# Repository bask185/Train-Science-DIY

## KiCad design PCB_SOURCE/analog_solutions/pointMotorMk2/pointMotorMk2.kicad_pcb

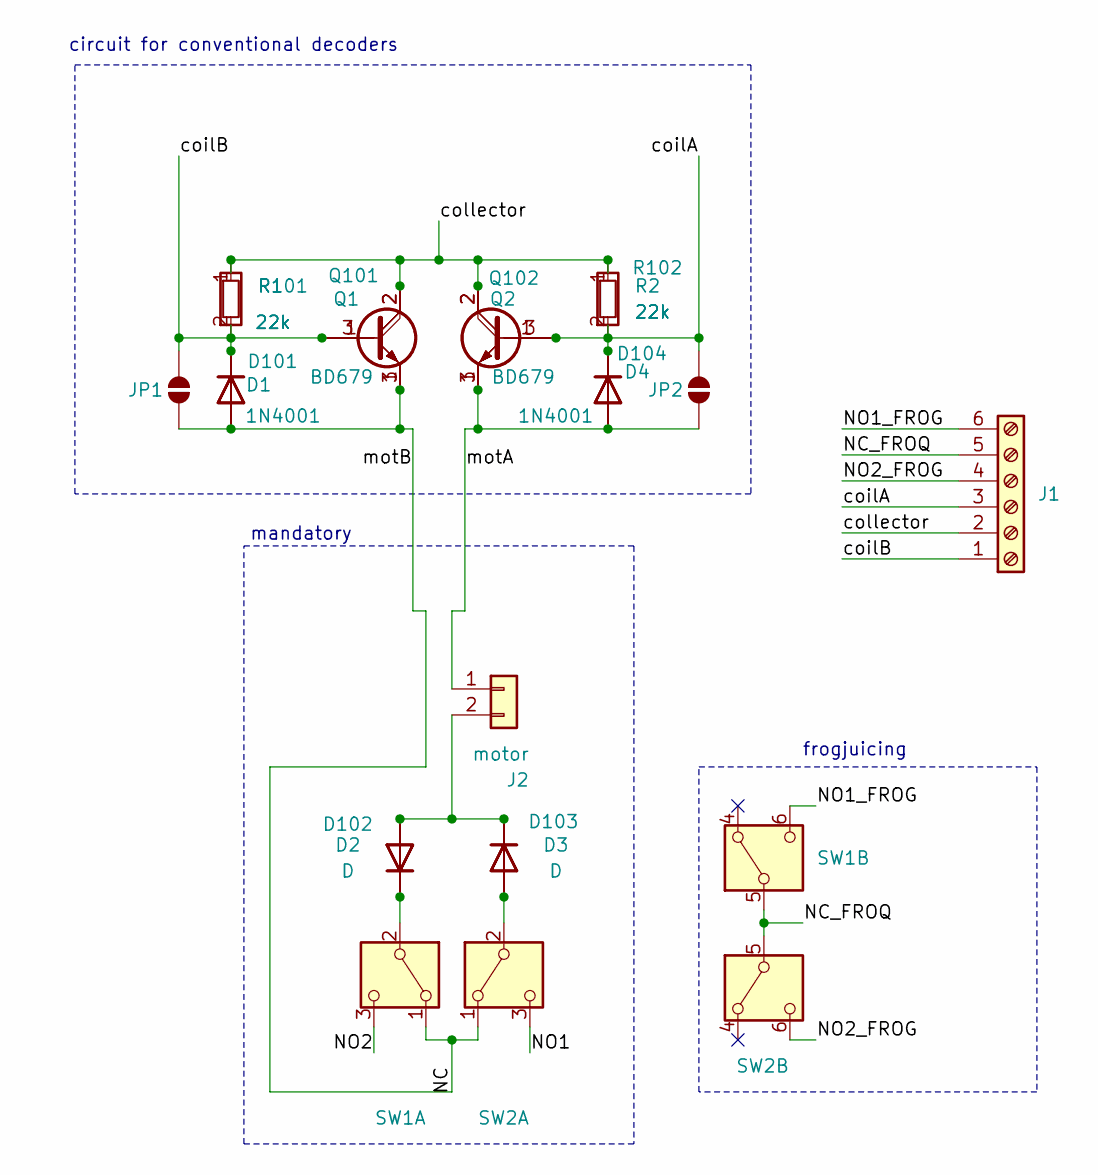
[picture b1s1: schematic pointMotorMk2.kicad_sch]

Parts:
D1, D4: 1N4001; D_DO-34_SOD68_P7.62mm_Horizontal
D2, D3: D; D_DO-34_SOD68_P7.62mm_Horizontal
D101, D102, D103, D104: SS26F; D_SMA; JLCPCB Part# C2758577
J1: Screw_Terminal_01x06; PhoenixContact_MCV_1,5_6-G-3.5_1x06_P3.50mm_Vertical
J2: motor; N20_motor_Mk2
JP1, JP2: SolderJumper_2_Open; SolderJumper-2_P1.3mm_Open_RoundedPad1.0x1.5mm
Q1, Q2: BD679; TO-126-3_Vertical
Q101, Q102: 4A_DARLINGTON; SOT-89-3; JLCPCB Part# C155228
R1, R2: 22k; R_Axial_DIN0204_L3.6mm_D1.6mm_P7.62mm_Horizontal
R101, R102: 22k; R_0805_handsolder-smalltext; JLCPCB Part# C17560
SW1, SW2: SW_DPDT_x2; DPDT_LIMIT_SWITCH

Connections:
/NC: D1.2 (A), D101.2 (A), JP1.1 (A), Q1.1 (E), Q101.3 (E), SW1.1 (A), SW2.1 (A)
/NC_FROQ: J1.5, SW1.5 (B), SW2.5 (B)
/NO1: SW2.3 (C)
/NO1_FROG: J1.6, SW1.6 (C)
/NO2: SW1.3 (C)
/NO2_FROG: J1.4, SW2.6 (C)
/coilA: D4.1 (K), D104.1 (K), J1.3, JP2.2 (B), Q2.3 (B), Q102.1 (B), R2.2, R102.2
/coilB: D1.1 (K), D101.1 (K), J1.1, JP1.2 (B), Q1.3 (B), Q101.1 (B), R1.2, R101.2
/collector: J1.2, Q1.2 (C), Q2.2 (C), Q101.2 (C), Q102.2 (C), R1.1, R2.1, R101.1, R102.1
/motA: D4.2 (A), D104.2 (A), J2.1, JP2.1 (A), Q2.1 (E), Q102.3 (E)
unnamed: D2.2 (A), D3.1 (K), D102.2 (A), D103.1 (K), J2.2
unnamed: D2.1 (K), D102.1 (K), SW1.2 (B)
unnamed: D3.2 (A), D103.2 (A), SW2.2 (B)

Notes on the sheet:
frogjuicing
mandatory
circuit for conventional decoders

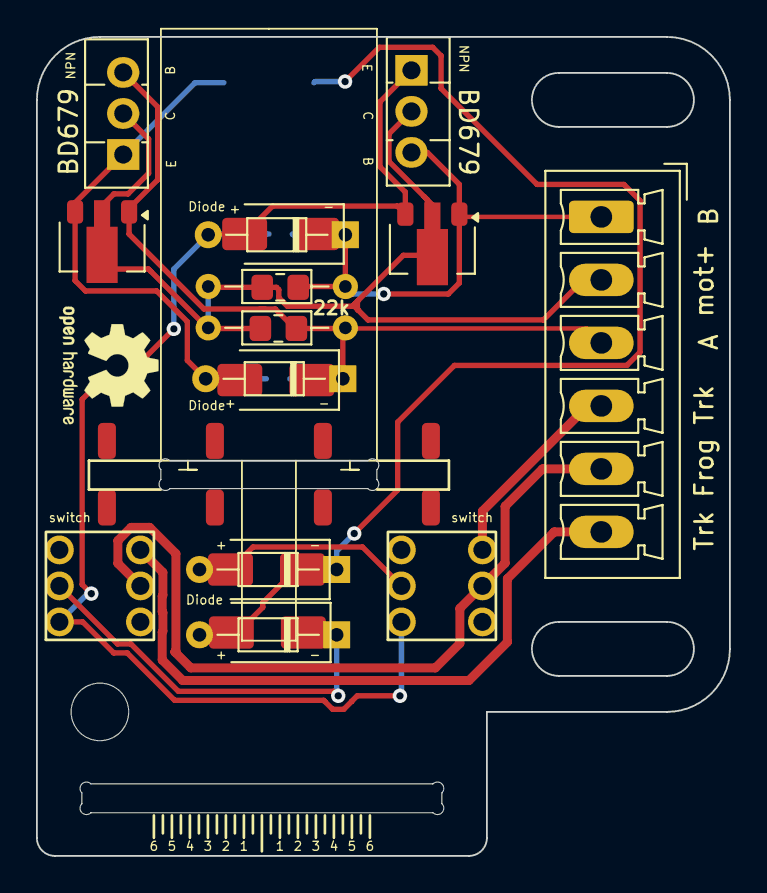
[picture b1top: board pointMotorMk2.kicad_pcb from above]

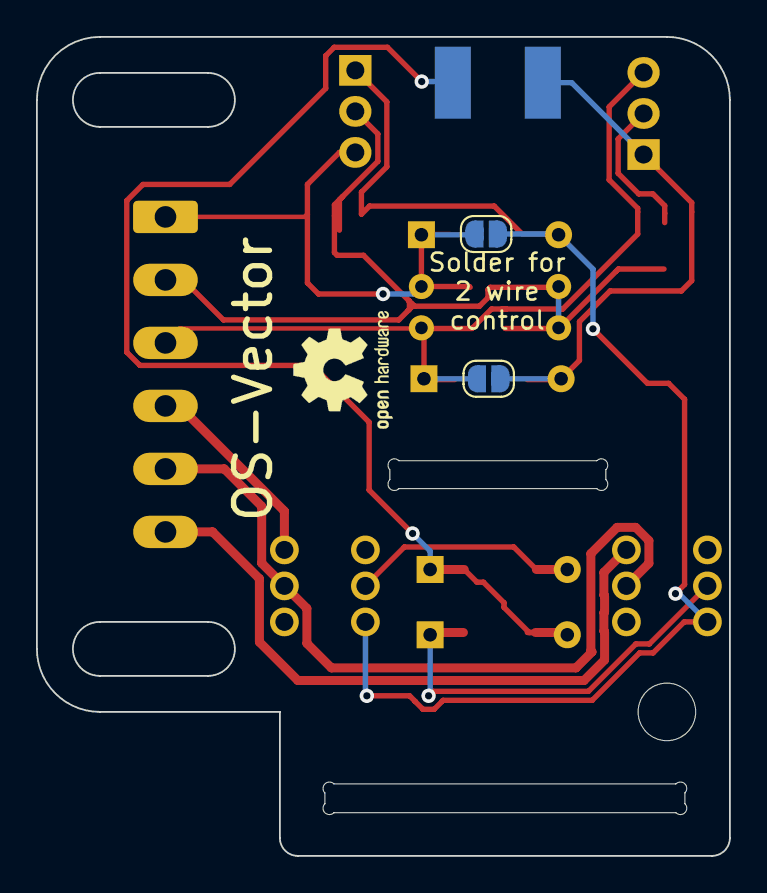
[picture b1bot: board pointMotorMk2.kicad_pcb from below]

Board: 2 copper layers, 38.5 x 45.5 mm, 23 parts (2 on the bottom side), 11 nets.

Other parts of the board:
**: slideGuide

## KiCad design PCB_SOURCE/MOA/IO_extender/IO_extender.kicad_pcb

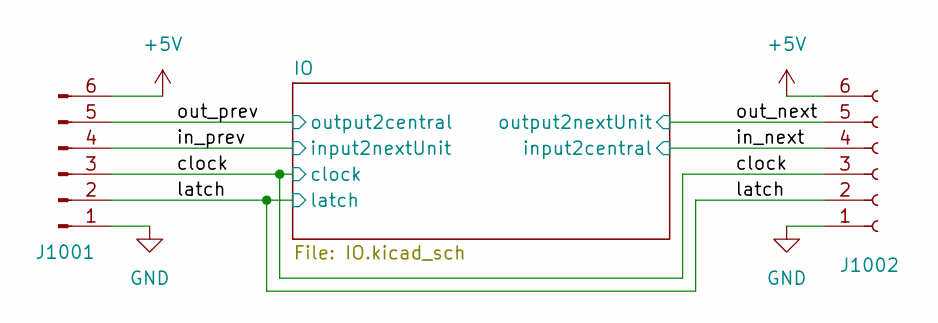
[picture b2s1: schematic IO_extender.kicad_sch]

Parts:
J1001: Conn_01x06_Pin; PinHeader_1x06_P2.54mm_Horizontal
J1002: Conn_01x06_Socket; PinSocket_1x06_P2.54mm_Horizontal

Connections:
+5V: J1001.6, J1002.6; also elsewhere on the board
/clock: J1001.3, J1002.3; also elsewhere on the board
/in_next: J1002.4; also elsewhere on the board
/in_prev: J1001.4; also elsewhere on the board
/latch: J1001.2, J1002.2; also elsewhere on the board
/out_next: J1002.5; also elsewhere on the board
/out_prev: J1001.5; also elsewhere on the board
GND: J1001.1, J1002.1; also elsewhere on the board

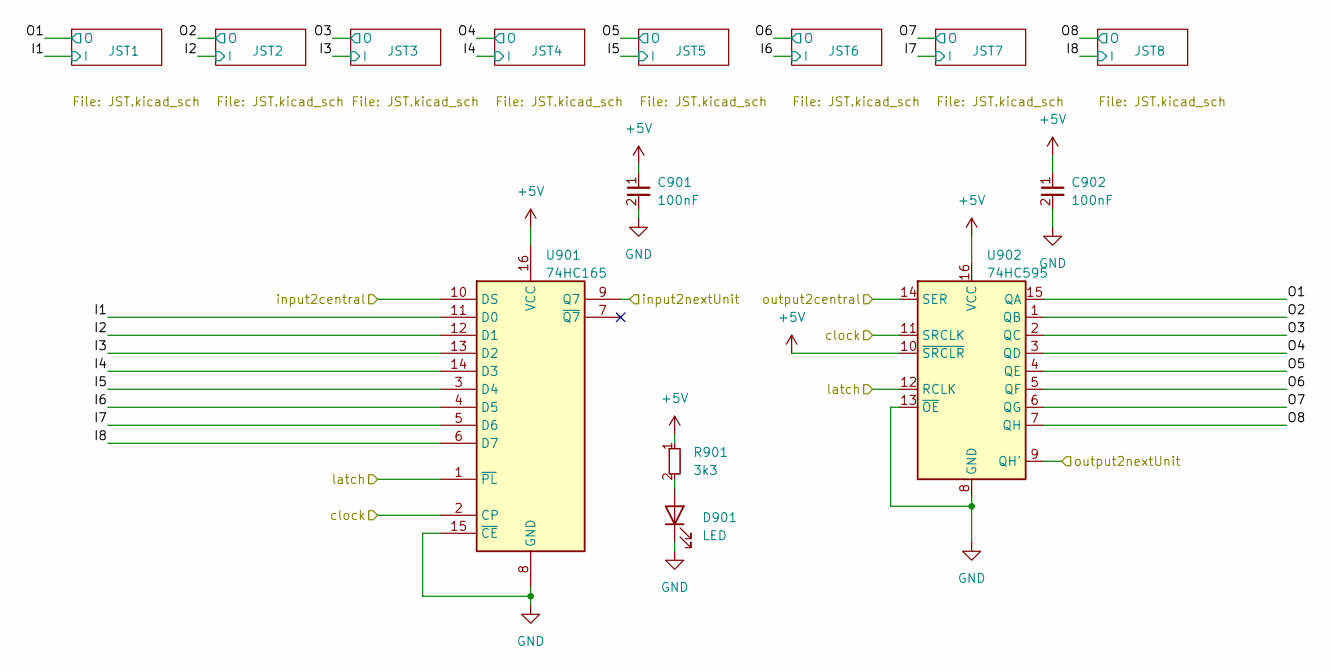
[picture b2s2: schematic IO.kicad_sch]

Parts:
C901, C902: 100nF; C_0603_1608Metric; JLCPCB Part# C14663
D901: LED; LED_0805_2012Metric_Pad1.15x1.40mm_HandSolder; JLCPCB Part# C2296
R901: 3k3; R_0603_smalltext; JLCPCB Part# C22978
U901: 74HC165; SOIC-16_3.9x9.9mm_P1.27mm; JLCPCB Part# C5613
U902: 74HC595; SOIC-16_3.9x9.9mm_P1.27mm; JLCPCB Part# C5947

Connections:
+5V: C901.1, C902.1, R901.1, U901.16 (VCC), U902.10 (~SRCLR), U902.16 (VCC); also elsewhere on the board
/IO/I1: U901.11 (D0); also elsewhere on the board
/IO/I2: U901.12 (D1); also elsewhere on the board
/IO/I3: U901.13 (D2); also elsewhere on the board
/IO/I4: U901.14 (D3); also elsewhere on the board
/IO/I5: U901.3 (D4); also elsewhere on the board
/IO/I6: U901.4 (D5); also elsewhere on the board
/IO/I7: U901.5 (D6); also elsewhere on the board
/IO/I8: U901.6 (D7); also elsewhere on the board
/IO/O1: U902.15 (QA); also elsewhere on the board
/IO/O2: U902.1 (QB); also elsewhere on the board
/IO/O3: U902.2 (QC); also elsewhere on the board
/IO/O4: U902.3 (QD); also elsewhere on the board
/IO/O5: U902.4 (QE); also elsewhere on the board
/IO/O6: U902.5 (QF); also elsewhere on the board
/IO/O7: U902.6 (QG); also elsewhere on the board
/IO/O8: U902.7 (QH); also elsewhere on the board
/clock: U901.2 (CP), U902.11 (SRCLK); also elsewhere on the board
/in_next: U901.10 (DS); also elsewhere on the board
/in_prev: U901.9 (Q7); also elsewhere on the board
/latch: U901.1 (~PL), U902.12 (RCLK); also elsewhere on the board
/out_next: U902.9 (QH'); also elsewhere on the board
/out_prev: U902.14 (SER); also elsewhere on the board
GND: C901.2, C902.2, D901.1 (K), U901.8 (GND), U901.15 (~CE), U902.8 (GND), U902.13 (~OE); also elsewhere on the board
unnamed: D901.2 (A), R901.2

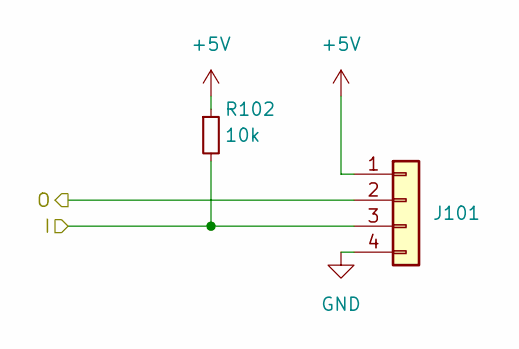
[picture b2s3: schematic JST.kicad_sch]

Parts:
J101: Conn_01x04; JST_SH_BM04B-SRSS-TB_1x04-1MP_P1.00mm_Vertical; JLCPCB Part# C160390
R102: 10k; R_0402_NO_SILK; JLCPCB Part# C25744

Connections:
+5V: J101.1, R102.1; also elsewhere on the board
/IO/I1: J101.3, R102.2; also elsewhere on the board
/IO/O1: J101.2; also elsewhere on the board
GND: J101.4; also elsewhere on the board

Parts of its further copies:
J201, J301, J401, J501, J601, J701, J801: Conn_01x04; JST_SH_BM04B-SRSS-TB_1x04-1MP_P1.00mm_Vertical; JLCPCB Part# C160390
R202, R302, R402, R502, R602, R702, R802: 10k; R_0402_NO_SILK; JLCPCB Part# C25744

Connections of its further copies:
+5V: J201.1, J301.1, J401.1, J501.1, J601.1, J701.1, J801.1, R202.1, R302.1, R402.1, R502.1, R602.1, R702.1, R802.1; also elsewhere on the board
/IO/I2: J201.3, R202.2; also elsewhere on the board
/IO/I3: J301.3, R302.2; also elsewhere on the board
/IO/I4: J401.3, R402.2; also elsewhere on the board
/IO/I5: J501.3, R502.2; also elsewhere on the board
/IO/I6: J601.3, R602.2; also elsewhere on the board
/IO/I7: J701.3, R702.2; also elsewhere on the board
/IO/I8: J801.3, R802.2; also elsewhere on the board
/IO/O2: J201.2; also elsewhere on the board
/IO/O3: J301.2; also elsewhere on the board
/IO/O4: J401.2; also elsewhere on the board
/IO/O5: J501.2; also elsewhere on the board
/IO/O6: J601.2; also elsewhere on the board
/IO/O7: J701.2; also elsewhere on the board
/IO/O8: J801.2; also elsewhere on the board
GND: J201.4, J301.4, J401.4, J501.4, J601.4, J701.4, J801.4; also elsewhere on the board

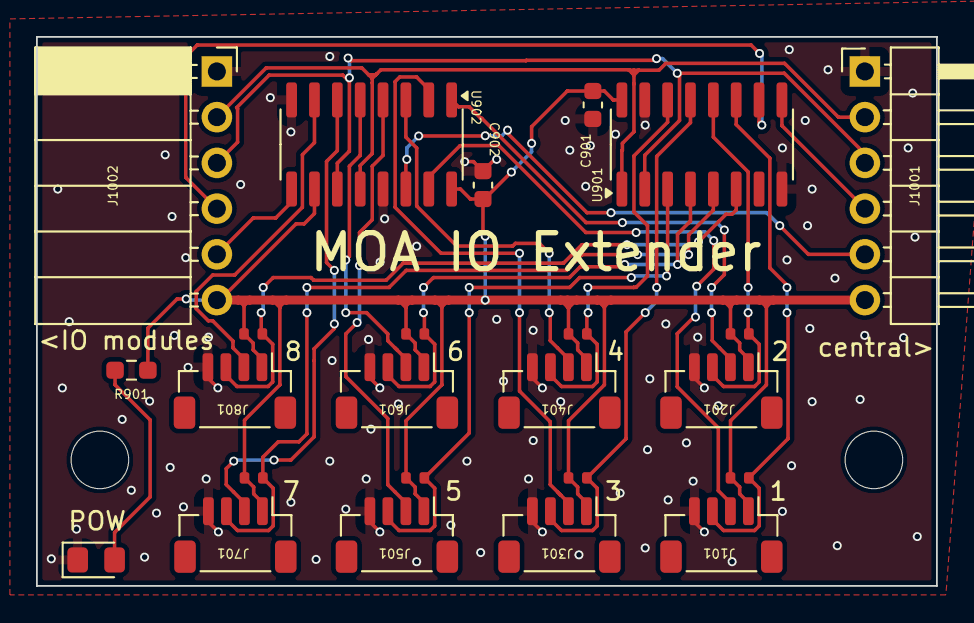
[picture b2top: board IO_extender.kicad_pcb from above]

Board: 2 copper layers, 50.0 x 30.5 mm, 24 parts (0 on the bottom side), 25 nets.

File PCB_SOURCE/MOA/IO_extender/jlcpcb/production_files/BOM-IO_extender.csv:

Comment,Designator,Footprint,LCSC
100nF,"C901,C902",C_0603_1608Metric,C14663
Conn_01x04,"J101,J201,J301,J401,J501,J601,J701,J801",JST_SH_BM04B-SRSS-TB_1x04-1MP_P1.00mm_Vertical,C160390
LED,D901,LED_0805_2012Metric_Pad1.15x1.40mm_HandSolder,C2296
3k3,R901,R_0603_smalltext,C22978
10k,"R102,R202,R302,R402,R502,R602,R702,R802",R_0402_NO_SILK,C25744
74HC165,U901,SOIC-16_3.9x9.9mm_P1.27mm,C5613
74HC595,U902,SOIC-16_3.9x9.9mm_P1.27mm,C5947

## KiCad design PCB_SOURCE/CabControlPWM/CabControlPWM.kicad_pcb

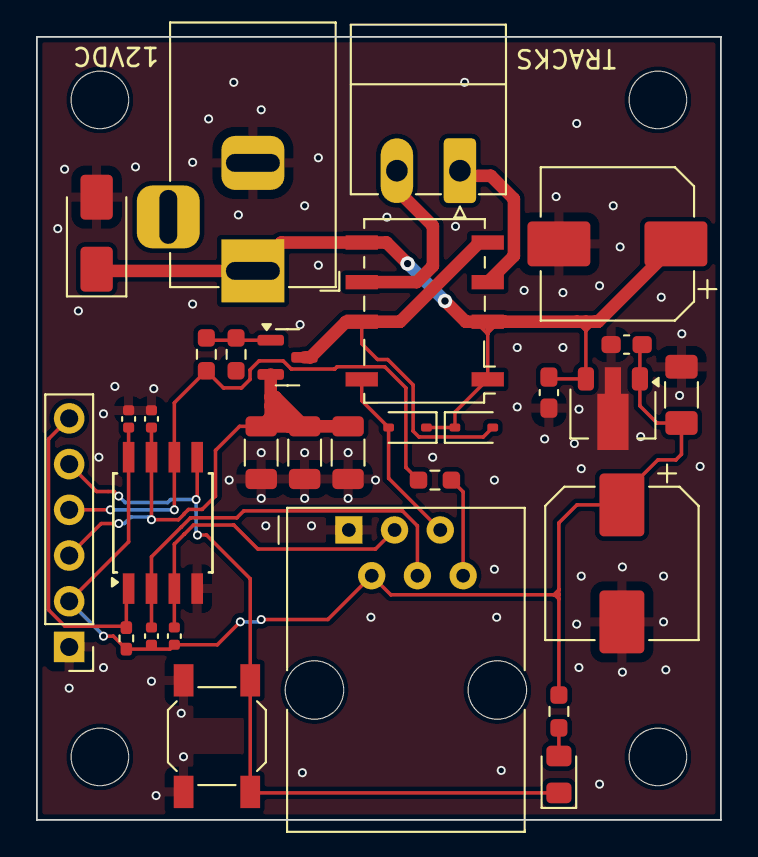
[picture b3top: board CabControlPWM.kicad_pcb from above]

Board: 2 copper layers, 38.0 x 43.5 mm, 30 parts (0 on the bottom side), 16 nets.

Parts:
C201, C401, C402, C501: 100nF; C_0402_1005Metric
C301: 330nF; C_0603_1608Metric_Pad1.08x0.95mm_HandSolder
C302: 100nF; C_0603_1608Metric_Pad1.08x0.95mm_HandSolder
C303: 100uF; C_1206_3216Metric_Pad1.33x1.80mm_HandSolder
C304, C305: 470uF; CP_Elec_8x10
D201: LED; LED_0805_2012Metric_Pad1.15x1.40mm_HandSolder
D401: D; D_SMA
D501, D502: 1N4148WS; D_SOD-323
J201: Conn_01x06_Pin; PinHeader_1x06_P2.54mm_Vertical
J301: Jack-DC; BarrelJack_Horizontal
J401: RJ12
J501: Screw_Terminal_01x02; PhoenixContact_MC_1,5_2-G-3.5_1x02_P3.50mm_Horizontal
K501: G6K-2F-Y-TR DC12; Relay_DPDT_Omron_G6K-2F-Y
Q501: AO3400A; SOT-23
R201: 10k; R_0402_1005Metric_Pad0.72x0.64mm_HandSolder
R202: 680R; R_0603_smalltext
R301: 220R; R_0603_smalltext
R501, R502, R503: 0R1; R_1206_3216Metric
R504: 22k; R_0603_smalltext
R505: 22R; R_0603_smalltext
SW201: default_switch
U201: ATtiny85-20S; SOIC-8W_5.3x5.3mm_P1.27mm
U301: L78L05_SOT89; SOT-89-3

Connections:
+5V: C201.1, C302.1, C303.1, C305.1, C401.2, C402.2, J201.2, J401.2, R201.1, R202.1, U201.8 (VCC), U301.1 (OUT)
+12V: C301.1, C304.1, D401.1 (K), D501.1 (K), D502.1 (K), J301.1, K501.1, K501.2, K501.5, U301.3 (IN)
/controls/CS: C501.1, J201.3, Q501.2 (S), R501.1, R502.1, R503.1, U201.7 (PB2)
/controls/PWM: J201.4, R301.1, R505.2, U201.6 (PB1)
/controls/brake: C402.1, J401.3, U201.3 (XTAL2/PB4)
/controls/dir: D501.2 (A), J401.5, K501.8
/controls/throttle: C401.1, J401.4, U201.2 (XTAL1/PB3)
/trackPower/J: J501.1, K501.3
/trackPower/K: J501.2, K501.6
/uProcessor/MOSI: D201.1 (K), J201.5, SW201.2 (B), U201.5 (AREF/PB0)
/uProcessor/RESET: J201.6, R201.2, U201.1 (~RESET/PB5)
GND: C201.2, C301.2, C302.2, C303.2, C304.2, C305.2, C501.2, D401.2 (A), J201.1, J301.2, J401.1, R501.2, R502.2, R503.2, R504.1, SW201.1 (A), U201.4 (GND), U301.2 (GND)
unnamed: D201.2 (A), R202.2
unnamed: D502.2 (A), K501.4, K501.7, Q501.3 (D)
unnamed: J401.6, R301.2
unnamed: Q501.1 (G), R504.2, R505.1

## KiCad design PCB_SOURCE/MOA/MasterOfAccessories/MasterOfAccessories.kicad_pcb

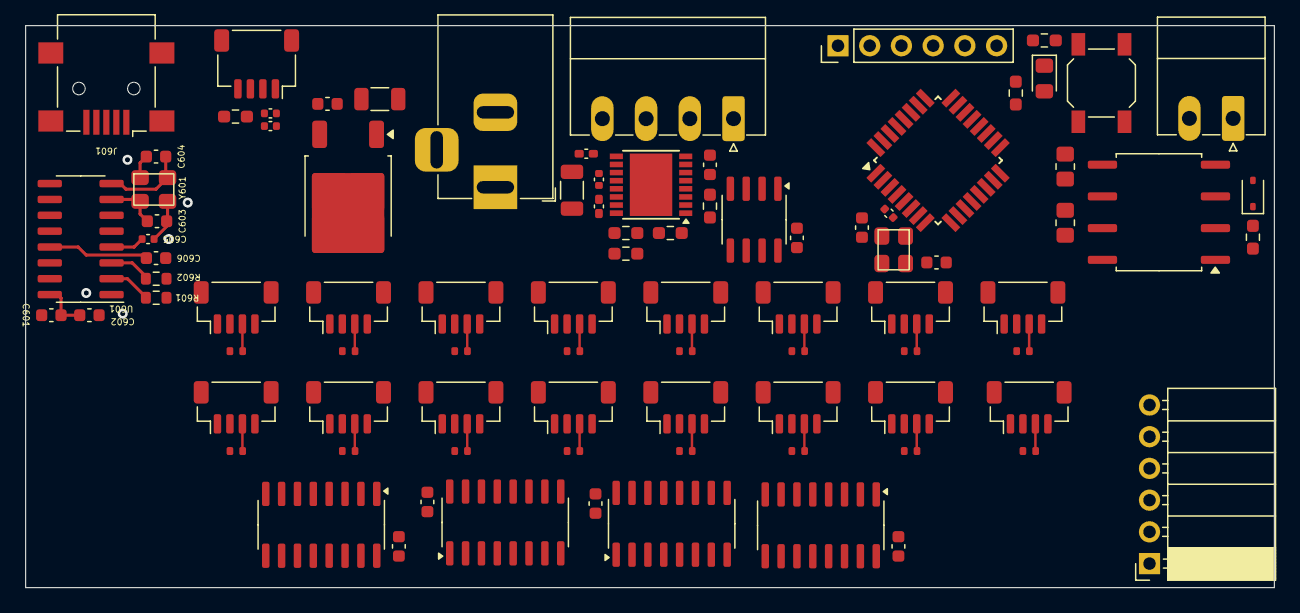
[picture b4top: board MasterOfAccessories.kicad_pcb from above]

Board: 2 copper layers, 100.0 x 45.0 mm, 89 parts (0 on the bottom side), 79 nets.

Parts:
C201, C203: 12pF; C_0603_1608Metric
C202, C502, C605, C801, C802: 100nF; C_0402_1005Metric
C301, C302, C402, C501, C602, C606, C901, C1401, C1402: 100nF; C_0603_1608Metric
C401: 47uF; C_1206_3216Metric
C503: 10uF; C_1206_3216Metric
C504: 22n VM; C_0402_1005Metric_Pad0.74x0.62mm_HandSolder
C505: 100nF; C_0402_1005Metric_Pad0.74x0.62mm_HandSolder
C601: 10uF; C_0603_1608Metric
C603, C604: 22pF; C_0603_1608Metric
D1001: 1N4148WS; D_SOD-323
D1101: LED; LED_0805_2012Metric_Pad1.15x1.40mm_HandSolder
J201: ICSP; PinHeader_1x06_P2.54mm_Vertical
J401: Jack-DC; BarrelJack_Horizontal
J501: FEMALE; PhoenixContact_MC_1,5_4-G-3.5_1x04_P3.50mm_Horizontal
J601: USB_B_Mini; USB_Mini-B_Lumberg_2486_01_Horizontal
J701: Conn_01x06_Socket; PinSocket_1x06_P2.54mm_Horizontal
J801: Conn_01x04_Socket; JST_SH_SM04B-SRSS-TB_1x04-1MP_P1.00mm_Horizontal
J1001: Screw_Terminal_01x02; PhoenixContact_MC_1,5_2-G-3.5_1x02_P3.50mm_Horizontal
J1501, J1601, J1701, J1801, J1901, J2001, J2101, J2201, J2301, J2401, J2501, J2601, J2701, J2801, J2901, J3001: Conn_01x04; jst_1.00_vert
R202, R801: 10k; R_0603_smalltext
R501: 680R; R_0603_smalltext
R502, R1001: 1k5; R_0603_smalltext
R503: 100R; R_0603_smalltext
R504: 47k; R_0603_smalltext
R601, R602: 1k; R_0603_1608Metric
R1002, R1003: 10k; R_0805_2012Metric_Pad1.20x1.40mm_HandSolder
R1101: 6k8; R_0603_smalltext
R1501, R1601, R1701, R1801, R1901, R2001, R2101, R2201, R2301, R2401, R2501, R2601, R2701, R2801, R2901, R3001: 10k; R_0402_NO_SILK
SW1101: default_switch
U201: ATmega328-A; TQFP-32_7x7mm_P0.8mm
U301, U1401: 74HC165; SOIC-16_3.9x9.9mm_P1.27mm
U302, U1402: 74HC595; SOIC-16_3.9x9.9mm_P1.27mm
U401: L7805; TO-252-2
U501: DRV8874; HTSSOP-16-1EP_4.4x5mm_P0.65mm_EP3.4x5mm
U601: CH340G; SOIC-16_3.9x9.9mm_P1.27mm
U901: 24LC256; SOIC-8_3.9x4.9mm_P1.27mm
U1001: 6N137; SOP-8_6.62x9.15mm_P2.54mm
Y201: Crystal_GND2; crystal_arduino
Y601: Crystal; crystal_arduino

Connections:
+5V: C202.1, C301.1, C302.1, C402.1, C501.1, C601.1, C602.1, C801.1, C802.1, C901.2, C1401.1, C1402.1, J201.2, J601.1 (VBUS), J701.6, J801.4, J1501.1, J1601.1, J1701.1, J1801.1, J1901.1, J2001.1, J2101.1, J2201.1, J2301.1, J2401.1, J2501.1, J2601.1, J2701.1, J2801.1, J2901.1, J3001.1, R202.1, R504.1, R801.1, R1002.1, R1003.1, R1501.1, R1601.1, R1701.1, R1801.1, R1901.1, R2001.1, R2101.1, R2201.1, R2301.1, R2401.1, R2501.1, R2601.1, R2701.1, R2801.1, R2901.1, R3001.1, U201.4 (VCC), U201.6 (VCC), U201.18 (AVCC), U301.16 (VCC), U302.10 (~SRCLR), U302.16 (VCC), U401.3 (OUT), U501.3 (nSleep), U501.5 (Vref), U501.16 (Pmode), U601.16 (VCC), U901.8 (VCC), U1001.8 (VCC), U1401.16 (VCC), U1402.10 (~SRCLR), U1402.16 (VCC)
+12V: C401.1, C502.1, C503.1, C505.1, J401.1, J501.1, U401.1 (IN), U501.11 (VM)
/DCC/DCC: R1003.2, U201.32 (PD2), U1001.6 (VO)
/EEPROM/SCL: U201.28 (PC5), U901.6 (SCL)
/EEPROM/SDA: U201.27 (PC4), U901.5 (SDA)
/Hbridge/IN.A: U201.12 (PB0), U501.1 (IN1)
/Hbridge/IN.B: U201.13 (PB1), U501.2 (IN2)
/Hbridge/IN.CS: R502.1, U201.26 (PC3), U501.6 (Ipropi)
/Hbridge/OUT.A: J501.3, U501.8 (OUT1)
/Hbridge/OUT.B: J501.4, U501.10 (OUT2)
/MCU/BUTTONS: C802.2, J801.3, R801.2, U201.19 (ADC6)
/MCU/LED: D1101.2 (A), U201.23 (PC0)
/MCU/MISO: J201.4, U201.16 (PB4)
/MCU/MOSI: J201.5, U201.15 (PB3)
/MCU/POT: C801.2, J801.2, U201.22 (ADC7)
/MCU/SCK: J201.3, U201.17 (PB5)
/MCU/S_Rx: R601.2, U201.30 (PD0)
/MCU/S_Tx: R602.1, U201.31 (PD1)
/MCU/Switch: SW1101.2 (B), U201.24 (PC1)
/MCU/X1: C201.2, U201.7 (XTAL1/PB6), Y201.1
/MCU/X2: C203.2, U201.8 (XTAL2/PB7), Y201.3
/MCU/central.clock: J701.3, U201.10 (PD6), U301.2 (CP), U302.11 (SRCLK), U1401.2 (CP), U1402.11 (SRCLK)
/MCU/central.in_prev: U201.2 (PD4), U301.9 (Q7)
/MCU/central.latch: J701.2, U201.11 (PD7), U301.1 (~PL), U302.12 (RCLK), U1401.1 (~PL), U1402.12 (RCLK)
/MCU/central.out_prev: U201.1 (PD3), U302.14 (SER)
/MCU/reset: C606.2, J201.6, R202.2, U201.29 (~RESET/PC6)
/shiftregisters1/IO.in_next: U301.10 (DS), U1401.10 (DS)
/shiftregisters1/IO.out_next: U302.9 (QH'), U1402.9 (QH')
/shiftregisters1/IO/I1: J1501.3, R1501.2, U301.11 (D0)
/shiftregisters1/IO/I2: J1601.3, R1601.2, U301.12 (D1)
/shiftregisters1/IO/I3: J1701.3, R1701.2, U301.13 (D2)
/shiftregisters1/IO/I4: J1801.3, R1801.2, U301.14 (D3)
/shiftregisters1/IO/I5: J1901.3, R1901.2, U301.3 (D4)
/shiftregisters1/IO/I6: J2001.3, R2001.2, U301.4 (D5)
/shiftregisters1/IO/I7: J2101.3, R2101.2, U301.5 (D6)
/shiftregisters1/IO/I8: J2201.3, R2201.2, U301.6 (D7)
/shiftregisters1/IO/O1: J1501.2, U302.15 (QA)
/shiftregisters1/IO/O2: J1601.2, U302.1 (QB)
/shiftregisters1/IO/O3: J1701.2, U302.2 (QC)
/shiftregisters1/IO/O4: J1801.2, U302.3 (QD)
/shiftregisters1/IO/O5: J1901.2, U302.4 (QE)
/shiftregisters1/IO/O6: J2001.2, U302.5 (QF)
/shiftregisters1/IO/O7: J2101.2, U302.6 (QG)
/shiftregisters1/IO/O8: J2201.2, U302.7 (QH)
/shiftregisters2/IO/I1: J2301.3, R2301.2, U1401.11 (D0)
/shiftregisters2/IO/I2: J2401.3, R2401.2, U1401.12 (D1)
/shiftregisters2/IO/I3: J2501.3, R2501.2, U1401.13 (D2)
/shiftregisters2/IO/I4: J2601.3, R2601.2, U1401.14 (D3)
/shiftregisters2/IO/I5: J2701.3, R2701.2, U1401.3 (D4)
/shiftregisters2/IO/I6: J2801.3, R2801.2, U1401.4 (D5)
/shiftregisters2/IO/I7: J2901.3, R2901.2, U1401.5 (D6)
/shiftregisters2/IO/I8: J3001.3, R3001.2, U1401.6 (D7)
/shiftregisters2/IO/O1: J2301.2, U1402.15 (QA)
/shiftregisters2/IO/O2: J2401.2, U1402.1 (QB)
/shiftregisters2/IO/O3: J2501.2, U1402.2 (QC)
/shiftregisters2/IO/O4: J2601.2, U1402.3 (QD)
/shiftregisters2/IO/O5: J2701.2, U1402.4 (QE)
/shiftregisters2/IO/O6: J2801.2, U1402.5 (QF)
/shiftregisters2/IO/O7: J2901.2, U1402.6 (QG)
/shiftregisters2/IO/O8: J3001.2, U1402.7 (QH)
GND: C201.1, C202.2, C203.1, C301.2, C302.2, C401.2, C402.2, C501.2, C503.2, C505.2, C601.2, C602.2, C603.2, C604.2, C605.1, C901.1, C1401.2, C1402.2, J201.1, J401.2, J501.2, J601.5 (GND), J601.6 (Shield), J701.1, J801.1, J1501.4, J1601.4, J1701.4, J1801.4, J1901.4, J2001.4, J2101.4, J2201.4, J2301.4, J2401.4, J2501.4, J2601.4, J2701.4, J2801.4, J2901.4, J3001.4, R501.2, R503.2, R1101.2, SW1101.1 (A), U201.3 (GND), U201.5 (GND), U201.21 (GND), U301.8 (GND), U301.15 (~CE), U302.8 (GND), U302.13 (~OE), U401.2 (GND), U501.7 (Imode), U501.9 (PGND), U501.15 (GND), U501.17 (GND), U601.1 (GND), U901.1 (A0), U901.2 (A1), U901.3 (A2), U901.4 (GND), U901.7 (WP), U1001.5 (GND), U1401.8 (GND), U1401.15 (~CE), U1402.8 (GND), U1402.13 (~OE), Y201.2 (GND), Y201.4 (GND), Y601.2 (GND), Y601.4 (GND)
unnamed: D1001.2 (A), J1001.1, U1001.3 (C)
unnamed: D1001.1 (K), R1001.2, U1001.2 (A)
unnamed: D1101.1 (K), R1101.1
unnamed: J601.3 (D+), U601.5 (UD+)
unnamed: J601.2 (D-), U601.6 (UD-)
unnamed: J1001.2, R1001.1
unnamed: R501.1, R502.2, R503.1
unnamed: C504.1, U501.13 (CPH)
unnamed: C504.2, U501.14 (CPL)
unnamed: C502.2, U501.12 (VCP)
unnamed: R504.2, U501.4 (nFault)
unnamed: R602.2, U601.3 (RXD)
unnamed: R601.1, U601.2 (TXD)
unnamed: C605.2, U601.4 (V3)
unnamed: C603.1, U601.7 (XI), Y601.1
unnamed: C604.1, U601.8 (XO), Y601.3
unnamed: C606.1, U601.13 (~DTR)
unnamed: R1002.2, U1001.7 (EN)

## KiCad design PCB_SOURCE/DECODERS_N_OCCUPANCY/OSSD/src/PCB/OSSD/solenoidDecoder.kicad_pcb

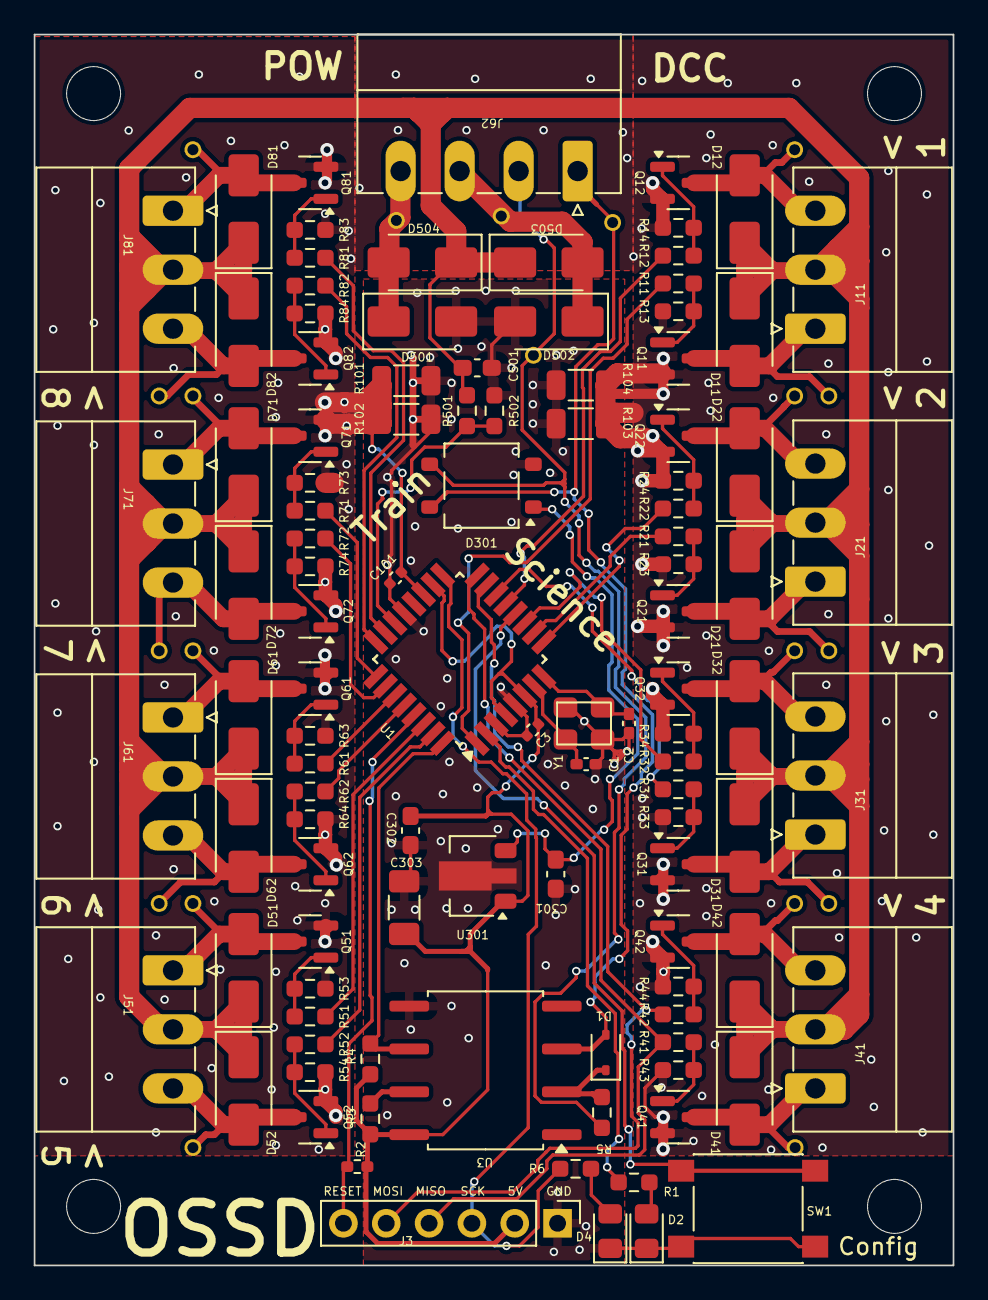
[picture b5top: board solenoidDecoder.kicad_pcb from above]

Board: 2 copper layers, 54.5 x 73.0 mm, 127 parts (0 on the bottom side), 69 nets.

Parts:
C1, C2: 12pF; C_0402_1005Metric_Pad0.74x0.62mm_HandSolder
C3, C101: 100nF; C_0402_1005Metric
C301: 330nF; C_0603_1608Metric_Pad1.08x0.95mm_HandSolder
C302, C501: 100nF; C_0603_1608Metric_Pad1.08x0.95mm_HandSolder
C303: 100uF; C_1206_3216Metric_Pad1.33x1.80mm_HandSolder
D1: D; D_SOD-323
D2, D4: LED; LED_0805_2012Metric_Pad1.15x1.40mm_HandSolder
D11, D21, D31, D41, D51, D61, D71, D81: SS34; D_SMA
D12, D22, D32, D42, D52, D62, D72, D82: D_SMA
D301: MB10S; TO-269AA
D501, D502, D503, D504: SS53; D_SMA
J3: ICSP; PinHeader_1x06_P2.54mm_Vertical
J11, J21, J31, J41, J51, J61, J71, J81: PhoenixContact_MC_1,5_3-G-3.5_1x03_P3.50mm_Horizontal
J62: Screw_Terminal_01x04; PhoenixContact_MC_1,5_4-G-3.5_1x04_P3.50mm_Horizontal
Q11, Q12, Q21, Q22, Q31, Q32, Q41, Q42, Q51, Q52, Q61, Q62, Q71, Q72, Q81, Q82: AO3400A; SOT-23
R1, R3, R4, R502: 10k; R_0603_smalltext
R2: 10k; R_0402_1005Metric_Pad0.72x0.64mm_HandSolder
R5: 1k5; R_0603_smalltext
R6: 6k2; R_0603_1608Metric_Pad0.98x0.95mm_HandSolder
R11, R12, R21, R22, R31, R32, R41, R42, R51, R52, R61, R62, R71, R72, R81, R82: 22R; R_0603_1608Metric_Pad0.98x0.95mm_HandSolder
R13, R14, R23, R24, R33, R34, R43, R44, R53, R54, R63, R64, R73, R74, R83, R84: 10k; R_0603_1608Metric_Pad0.98x0.95mm_HandSolder
R101, R102, R103, R104: 0R1; R_1206_3216Metric
R501: 47k; R_0603_smalltext
SW1: SW_SPST; tactile_SMD_6mm
TP1, TP2, TP3, TP4, TP5, TP6, TP7, TP8, TP9, TP10, TP11, TP12, TP13, TP14, TP15, TP16, TP17, TP18, TP19, TP20: TestPoint; pogoTestPad
U1: ATmega328-A; TQFP-32_7x7mm_P0.8mm
U3: 6N137; SOP-8_6.62x9.15mm_P2.54mm
U301: L78L05_SOT89; SOT-89-3
Y1: Crystal_GND2; crystal_arduino

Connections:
+5V: C3.1, C302.1, C303.1, J3.2, R2.1, R3.1, R4.1, U1.4 (VCC), U1.6 (VCC), U1.18 (AVCC), U3.8 (VCC), U301.1 (OUT)
/DCC/A: D1.2 (A), D301.4, J62.1, TP17.1, U3.3 (C)
/DCC/B: D301.3, J62.2, R5.1, TP18.1
/DCC/DCC_TTL: R4.2, U1.32 (PD2), U3.6 (VO)
/POWER/A: D501.1 (K), D504.2 (A), J62.4, TP19.1
/POWER/B: D502.1 (K), D503.2 (A), J62.3, TP20.1
/POWER/coilVoltage: R501.2, R502.1, U1.22 (ADC7)
/mosfets1/A: R12.1, U1.13 (PB1)
/mosfets1/B: R11.1, U1.1 (PD3)
/mosfets2/A: R22.1, U1.9 (PD5)
/mosfets2/B: R21.1, U1.10 (PD6)
/mosfets3/A: R32.1, U1.11 (PD7)
/mosfets3/B: R31.1, U1.14 (PB2)
/mosfets4/A: J3.5, R42.1, U1.15 (PB3)
/mosfets4/B: J3.4, R41.1, U1.16 (PB4)
/mosfets5/A: R52.1, U1.31 (PD1)
/mosfets5/B: R51.1, U1.30 (PD0)
/mosfets6/A: R62.1, U1.28 (PC5)
/mosfets6/B: R61.1, U1.27 (PC4)
/mosfets7/A: R72.1, U1.26 (PC3)
/mosfets7/B: R71.1, U1.25 (PC2)
/mosfets8/A: R82.1, U1.24 (PC1)
/mosfets8/B: R81.1, U1.23 (PC0)
/uController/LED: J3.3, R6.1, U1.17 (PB5)
/uController/LED_BLUE: R1.1, U1.2 (PD4)
/uController/RESET: J3.6, R2.2, U1.29 (~RESET/PC6)
/uController/X1: C1.2, U1.7 (XTAL1/PB6), Y1.1
/uController/X2: C2.2, U1.8 (XTAL2/PB7), Y1.3
GND: C1.1, C2.1, C3.2, C101.2, C301.2, C302.2, C303.2, C501.2, D2.1 (K), D4.1 (K), D301.2 (-), D501.2 (A), D502.2 (A), J3.1, R101.2, R102.2, R103.2, R104.2, R502.2, SW1.2 (B), U1.3 (GND), U1.5 (GND), U1.21 (GND), U3.5 (GND), U301.2 (GND), Y1.2 (GND), Y1.4 (GND)
GND_COIL: C101.1, Q11.2 (S), Q12.2 (S), Q21.2 (S), Q22.2 (S), Q31.2 (S), Q32.2 (S), Q41.2 (S), Q42.2 (S), Q51.2 (S), Q52.2 (S), Q61.2 (S), Q62.2 (S), Q71.2 (S), Q72.2 (S), Q81.2 (S), Q82.2 (S), R13.1, R14.1, R23.1, R24.1, R33.1, R34.1, R43.1, R44.1, R53.1, R54.1, R63.1, R64.1, R73.1, R74.1, R83.1, R84.1, R101.1, R102.1, R103.1, R104.1, U1.19 (ADC6)
unnamed: D1.1 (K), R5.2, U3.2 (A)
unnamed: D2.2 (A), R1.2
unnamed: D4.2 (A), R6.2
unnamed: D11.2 (A), J11.1, Q11.3 (D), TP3.1
unnamed: D12.2 (A), J11.3, Q12.3 (D), TP4.1
unnamed: D21.2 (A), J21.1, Q21.3 (D), TP1.1
unnamed: D22.2 (A), J21.3, Q22.3 (D), TP2.1
unnamed: D31.2 (A), J31.1, Q31.3 (D), TP5.1
unnamed: D32.2 (A), J31.3, Q32.3 (D), TP6.1
unnamed: D41.2 (A), J41.1, Q41.3 (D), TP7.1
unnamed: D42.2 (A), J41.3, Q42.3 (D), TP8.1
unnamed: D51.2 (A), J51.1, Q51.3 (D), TP9.1
unnamed: D52.2 (A), J51.3, Q52.3 (D), TP10.1
unnamed: D61.2 (A), J61.1, Q61.3 (D), TP11.1
unnamed: D62.2 (A), J61.3, Q62.3 (D), TP12.1
unnamed: D71.2 (A), J71.1, Q71.3 (D), TP13.1
unnamed: D72.2 (A), J71.3, Q72.3 (D), TP14.1
unnamed: D81.2 (A), J81.1, Q81.3 (D), TP15.1
unnamed: D82.2 (A), J81.3, Q82.3 (D), TP16.1
unnamed: C301.1, D301.1 (+), U301.3 (IN)
unnamed: Q11.1 (G), R11.2, R13.2
unnamed: Q12.1 (G), R12.2, R14.2
unnamed: Q21.1 (G), R21.2, R23.2
unnamed: Q22.1 (G), R22.2, R24.2
unnamed: Q31.1 (G), R31.2, R33.2
unnamed: Q32.1 (G), R32.2, R34.2
unnamed: Q41.1 (G), R41.2, R43.2
unnamed: Q42.1 (G), R42.2, R44.2
unnamed: Q51.1 (G), R51.2, R53.2
unnamed: Q52.1 (G), R52.2, R54.2
unnamed: Q61.1 (G), R61.2, R63.2
unnamed: Q62.1 (G), R62.2, R64.2
unnamed: Q71.1 (G), R71.2, R73.2
unnamed: Q72.1 (G), R72.2, R74.2
unnamed: Q81.1 (G), R81.2, R83.2
unnamed: Q82.1 (G), R82.2, R84.2
unnamed: SW1.1 (A), U1.12 (PB0)
unnamed: R3.2, U3.7 (EN)
VCC: C501.1, D11.1 (K), D12.1 (K), D21.1 (K), D22.1 (K), D31.1 (K), D32.1 (K), D41.1 (K), D42.1 (K), D51.1 (K), D52.1 (K), D61.1 (K), D62.1 (K), D71.1 (K), D72.1 (K), D81.1 (K), D82.1 (K), D503.1 (K), D504.1 (K), J11.2, J21.2, J31.2, J41.2, J51.2, J61.2, J71.2, J81.2, R501.1

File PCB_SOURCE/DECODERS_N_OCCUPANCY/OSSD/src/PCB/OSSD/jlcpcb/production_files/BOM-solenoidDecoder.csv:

Comment,Designator,Footprint,LCSC
6N137,U3,SOP-8_6.62x9.15mm_P2.54mm,C110020
Crystal_GND2,Y1,crystal_arduino,C13738
100nF,"C302,C501",C_0603_1608Metric_Pad1.08x0.95mm_HandSolder,C14663
ATmega328-A,U1,TQFP-32_7x7mm_P0.8mm,C14877
100uF,C303,C_1206_3216Metric_Pad1.33x1.80mm_HandSolder,C15008
12pF,"C1,C2",C_0402_1005Metric_Pad0.74x0.62mm_HandSolder,C1547
330nF,C301,C_0603_1608Metric_Pad1.08x0.95mm_HandSolder,C1615
AO3400A,"Q11,Q12,Q21,Q22,Q31,Q32,Q41,Q42,Q51,Q52,Q61,Q62,Q71,Q72,Q81,Q82",SOT-23,C20917
D,D1,D_SOD-323,C2128
1k5,R5,R_0603_smalltext,C22843
22R,"R11,R12,R21,R22,R31,R32,R41,R42,R51,R52,R61,R62,R71,R72,R81,R82",R_0603_1608Metric_Pad0.98x0.95mm_HandSolder,C23345
MB10S,D301,TO-269AA,C2488
0R1,"R101,R102,R103,R104",R_1206_3216Metric,C25334
10k,R2,R_0402_1005Metric_Pad0.72x0.64mm_HandSolder,C25744
10k,"R1,R13,R14,R23,R24,R3,R33,R34,R4,R43,R44,R502,R53,R54,R63,R64,R73,R74,R83,R84",R_0603_smalltext,C25804
47k,R501,R_0603_smalltext,C25819
100nF,"C101,C3",C_0402_1005Metric,C307331
SW_SPST,SW1,tactile_SMD_6mm,C381050
6k2,R6,R_0603_1608Metric_Pad0.98x0.95mm_HandSolder,C4260
L78L05_SOT89,U301,SOT-89-3,C71136
LED,"D2,D4",LED_0805_2012Metric_Pad1.15x1.40mm_HandSolder,C84256
SS34,"D11,D12,D21,D22,D31,D32,D41,D42,D501,D502,D503,D504,D51,D52,D61,D62,D71,D72,D81,D82",D_SMA,C8678
~,"J11,J21,J31,J41,J51,J61,J71,J81","PhoenixContact_MC_1,5_3-G-3.5_1x03_P3.50mm_Horizontal",C880573
Screw_Terminal_01x04,J62,"PhoenixContact_MC_1,5_4-G-3.5_1x04_P3.50mm_Horizontal",C880574
ICSP,J3,PinHeader_1x06_P2.54mm_Vertical,
TestPoint,TP12,pogoTestPad,
TestPoint,TP2,pogoTestPad,
TestPoint,TP3,pogoTestPad,
TestPoint,TP20,pogoTestPad,
TestPoint,TP6,pogoTestPad,
TestPoint,TP16,pogoTestPad,
TestPoint,TP18,pogoTestPad,
TestPoint,TP7,pogoTestPad,
TestPoint,TP13,pogoTestPad,
TestPoint,TP1,pogoTestPad,
TestPoint,TP4,pogoTestPad,
TestPoint,TP19,pogoTestPad,
TestPoint,TP11,pogoTestPad,
TestPoint,TP8,pogoTestPad,
TestPoint,TP14,pogoTestPad,
TestPoint,TP15,pogoTestPad,
TestPoint,TP9,pogoTestPad,
TestPoint,TP10,pogoTestPad,
TestPoint,TP5,pogoTestPad,
TestPoint,TP17,pogoTestPad,
